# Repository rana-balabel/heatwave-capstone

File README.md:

# HeatWave 🔥

**AI-Powered Heatstroke Prediction Wearable**

University of Waterloo Engineering Capstone Design Project.

HeatWave is a wearable embedded system designed to assess heatstroke
risk using physiological and environmental sensor data.

## Capstone Poster

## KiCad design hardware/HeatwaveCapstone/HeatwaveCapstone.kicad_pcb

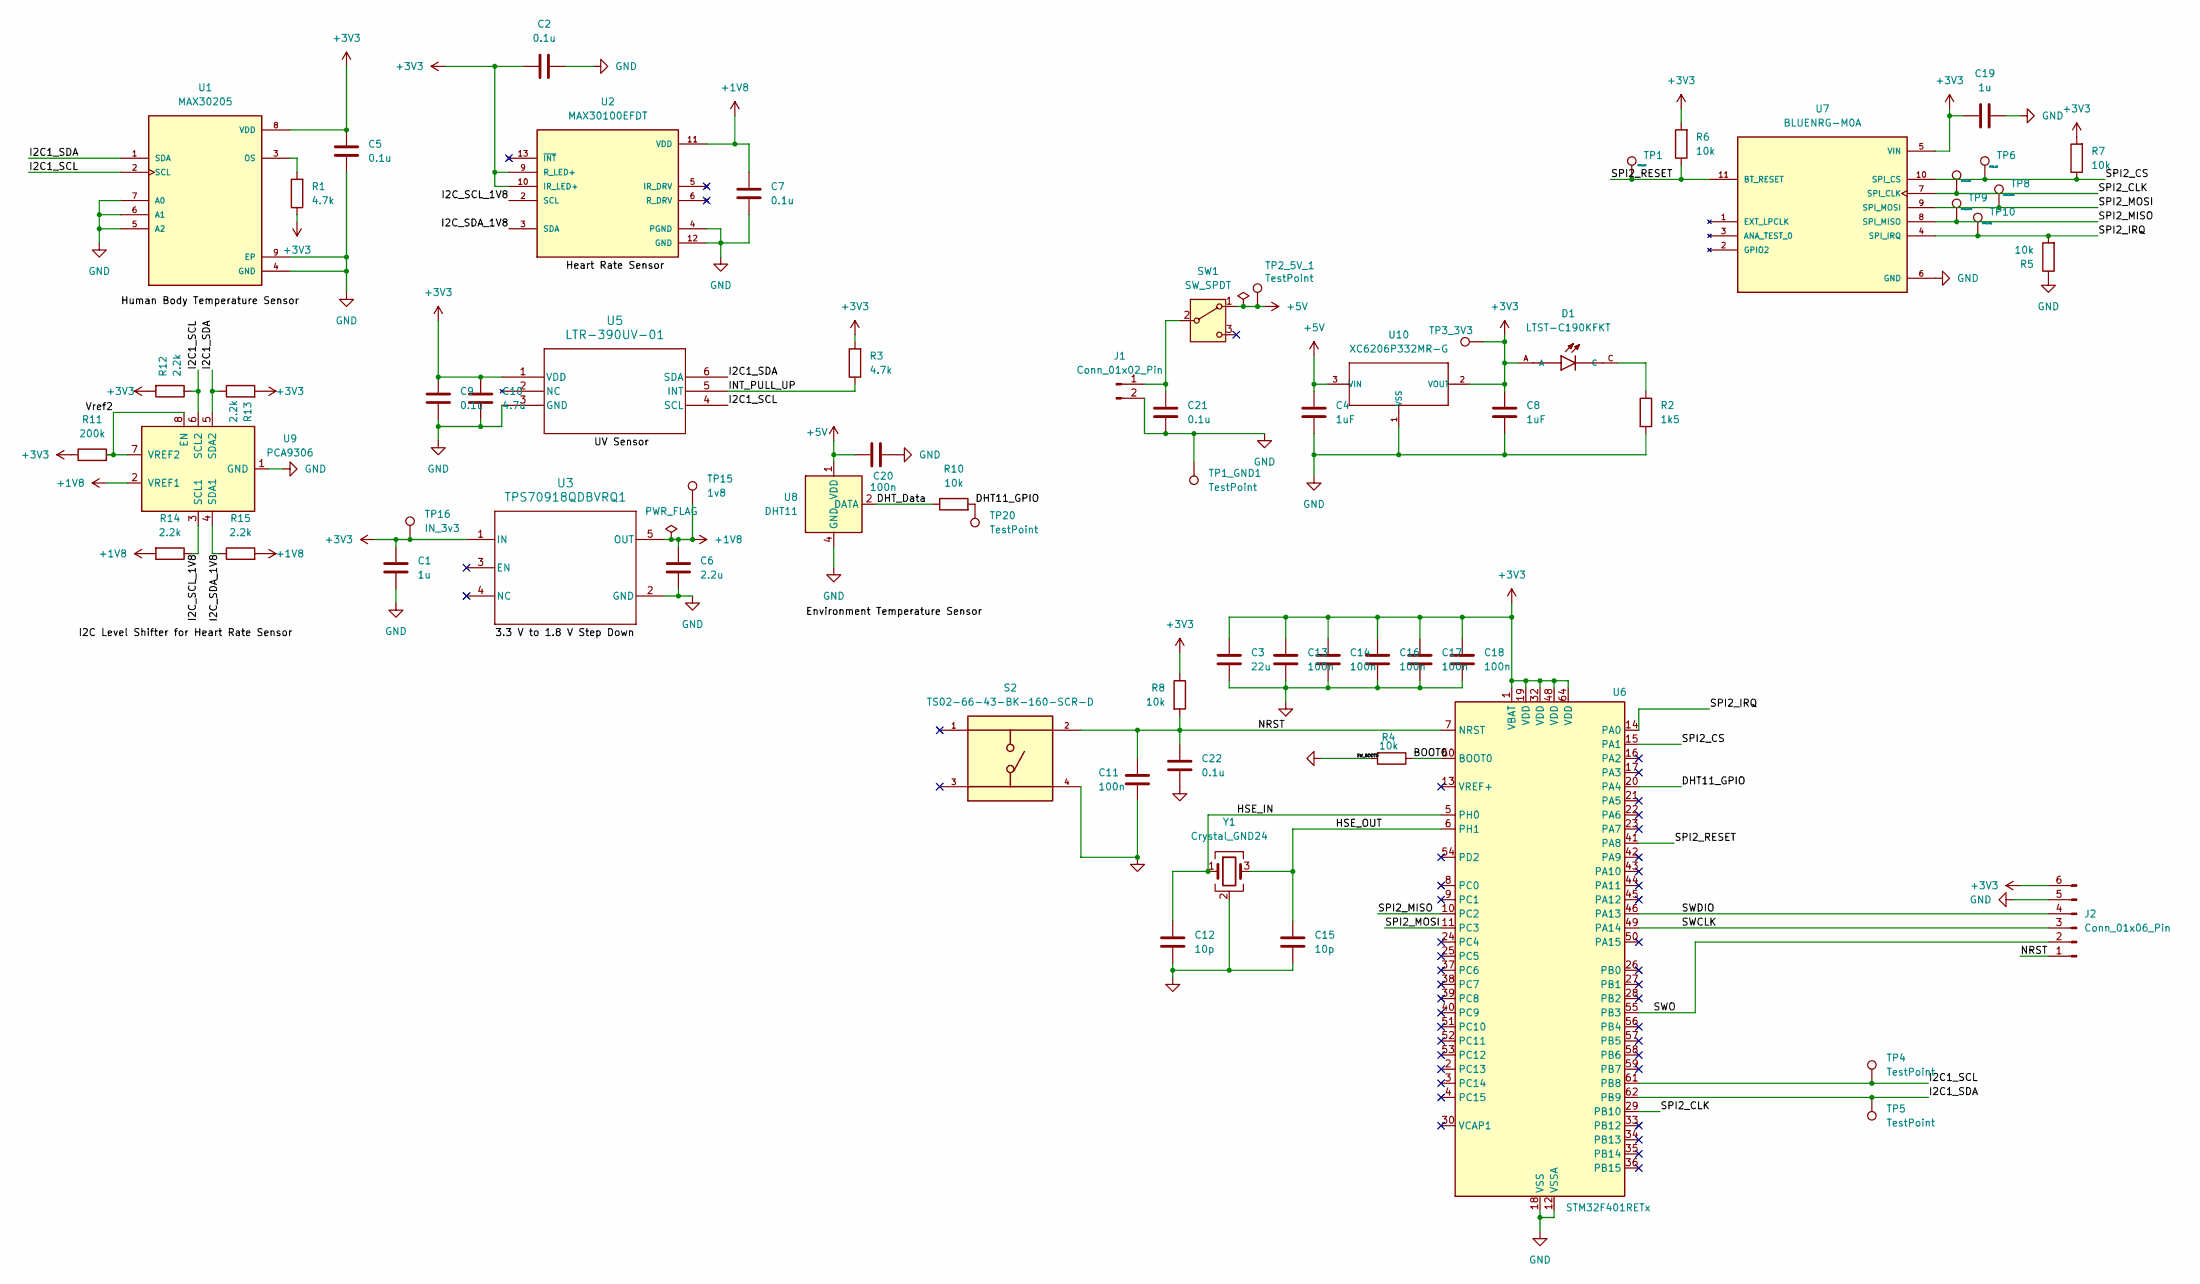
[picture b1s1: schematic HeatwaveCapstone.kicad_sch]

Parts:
C1, C19: 1u; C_0603_1608Metric
C2, C5, C7, C9, C21, C22: 0.1u; C_0603_1608Metric
C3: 22u; C_0603_1608Metric
C4, C8: 1uF; C_0603_1608Metric
C6: 2.2u; C_0603_1608Metric
C10: 4.7u; C_0603_1608Metric
C11, C13, C14, C16, C17, C18, C20: 100n; C_0603_1608Metric
C12, C15: 10p; C_0603_1608Metric
D1: LTST-C190KFKT; LEDM1608X80
J1: Conn_01x02_Pin; PinHeader_1x02_P2.54mm_Vertical
J2: Conn_01x06_Pin; PinHeader_1x06_P2.54mm_Vertical
R1, R3: 4.7k; R_0603_1608Metric
R2: 1k5; R_0603_1608Metric
R4, R5, R6, R7, R8, R10: 10k; R_0603_1608Metric
R11: 200k; R_0603_1608Metric
R12, R13, R14, R15: 2.2k; R_0603_1608Metric
S2: TS02-66-43-BK-160-SCR-D; SW_B3F-1000; PARTREV 1.0
SW1: SW_SPDT; SW_SPDT_CK_JS102011SAQN
TP1, TP6: SPI2_CS; TestPoint_Pad_1.0x1.0mm
TP1_GND1, TP2_5V_1, TP4, TP5, TP20: TestPoint; TestPoint_Pad_1.0x1.0mm
TP3_3V3: TestPoint_Pad_1.0x1.0mm
TP7: SPI2_CLK; TestPoint_Pad_1.0x1.0mm
TP8: SPI2_MOSI; TestPoint_Pad_1.0x1.0mm
TP9: SPI2_MISO; TestPoint_Pad_1.0x1.0mm
TP10: SPI2_IRQ; TestPoint_Pad_1.0x1.0mm
TP15: 1v8; TestPoint_Pad_1.0x1.0mm
TP16: IN_3v3; TestPoint_Pad_1.0x1.0mm
U1: MAX30205; SON65P300X300X80-9N
U2: MAX30100EFDT; LGA14R80P2X7_560X280X130
U3: TPS70918QDBVRQ1; SOT95P280X145-5N
U5: LTR-390UV-01; SMD6_LTR-390UV-01_LTO
U6: STM32F401RETx; LQFP-64_10x10mm_P0.5mm
U7: BLUENRG-M0A; XCVR_BLUENRG-M0A; PARTREV Rev 5
U8: DHT11; Aosong_DHT11_5.5x12.0_P2.54mm
U9: PCA9306; SOP65P400X130-8N
U10: XC6206P332MR-G; SOT-23; MPN XC6206P332MR-G
Y1: Crystal_GND24; XTAL_ABM8-16.000MHZ-10-1-U-T

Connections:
+1V8: C6.1, C7.1, R14.2, R15.2, TP15.1, U2.11 (VDD), U3.5 (OUT), U9.2 (VREF1)
+3V3: C1.1, C2.1, C3.1, C5.1, C8.1, C9.1, C10.1, C13.1, C14.1, C16.1, C17.1, C18.1, C19.1, D1.A, J2.6, R1.1, R3.2, R6.2, R7.2, R8.1, R11.1, R12.2, R13.2, TP3_3V3.1, TP16.1, U1.8 (VDD), U2.9 (R_LED+), U2.10 (IR_LED+), U3.1 (IN), U5.1 (VDD), U6.1 (VBAT), U6.19 (VDD), U6.32 (VDD), U6.48 (VDD), U6.64 (VDD), U7.5 (VIN), U10.2 (VOUT)
+5V: C4.1, C20.1, SW1.1 (A), TP2_5V_1.1, U8.1 (VDD), U10.3 (VIN)
/BOOT0: R4.1, U6.60 (BOOT0)
/DHT11_GPIO: R10.2, TP20.1, U6.20 (PA4)
/DHT_Data: R10.1, U8.2 (DATA)
/HSE_IN: C12.1, U6.5 (PH0), Y1.1
/HSE_OUT: C15.1, U6.6 (PH1), Y1.3
/I2C1_SCL: R12.1, TP4.1, U1.2 (SCL), U5.4 (SCL), U6.61 (PB8), U9.6 (SCL2)
/I2C1_SDA: R13.1, TP5.1, U1.1 (SDA), U5.6 (SDA), U6.62 (PB9), U9.5 (SDA2)
/I2C_SCL_1V8: R14.1, U2.2 (SCL), U9.3 (SCL1); also elsewhere on the board
/I2C_SDA_1V8: R15.1, U2.3 (SDA), U9.4 (SDA1); also elsewhere on the board
/INT_PULL_UP: R3.1, U5.5 (INT)
/NRST: C11.1, C22.2, J2.1, R8.2, S2.2, U6.7 (NRST)
/SPI2_CLK: TP7.1, U6.29 (PB10), U7.7 (SPI_CLK)
/SPI2_CS: R7.1, TP6.1, U6.15 (PA1), U7.10 (SPI_CS)
/SPI2_IRQ: R5.2, TP10.1, U6.14 (PA0), U7.4 (SPI_IRQ)
/SPI2_MISO: TP9.1, U6.10 (PC2), U7.8 (SPI_MISO)
/SPI2_MOSI: TP8.1, U6.11 (PC3), U7.9 (SPI_MOSI)
/SPI2_RESET: R6.1, TP1.1, U6.41 (PA8), U7.11 (BT_RESET)
/SWCLK: J2.3, U6.49 (PA14)
/SWDIO: J2.4, U6.46 (PA13)
/SWO: J2.2, U6.55 (PB3)
/Vref2: R11.2, U9.7 (VREF2), U9.8 (EN)
GND: C1.2, C2.2, C3.2, C4.2, C5.2, C6.2, C7.2, C8.2, C9.2, C10.2, C11.2, C12.2, C13.2, C14.2, C15.2, C16.2, C17.2, C18.2, C19.2, C20.2, C21.2, C22.1, J1.2, J2.5, R2.2, R4.2, R5.1, S2.4, TP1_GND1.1, U1.4 (GND), U1.5 (A2), U1.6 (A1), U1.7 (A0), U1.9 (EP), U2.4 (PGND), U2.12 (GND), U3.2 (GND), U5.3 (GND), U6.12 (VSSA), U6.18 (VSS), U6.31 (VSS), U6.47 (VSS), U6.63 (VSS), U7.6 (GND), U8.4 (GND), U9.1 (GND), U10.1 (VSS), Y1.2 (G), Y1.4 (G)
unnamed: D1.C, R2.1
unnamed: C21.1, J1.1, SW1.2 (B)
unnamed: R1.2, U1.3 (OS)

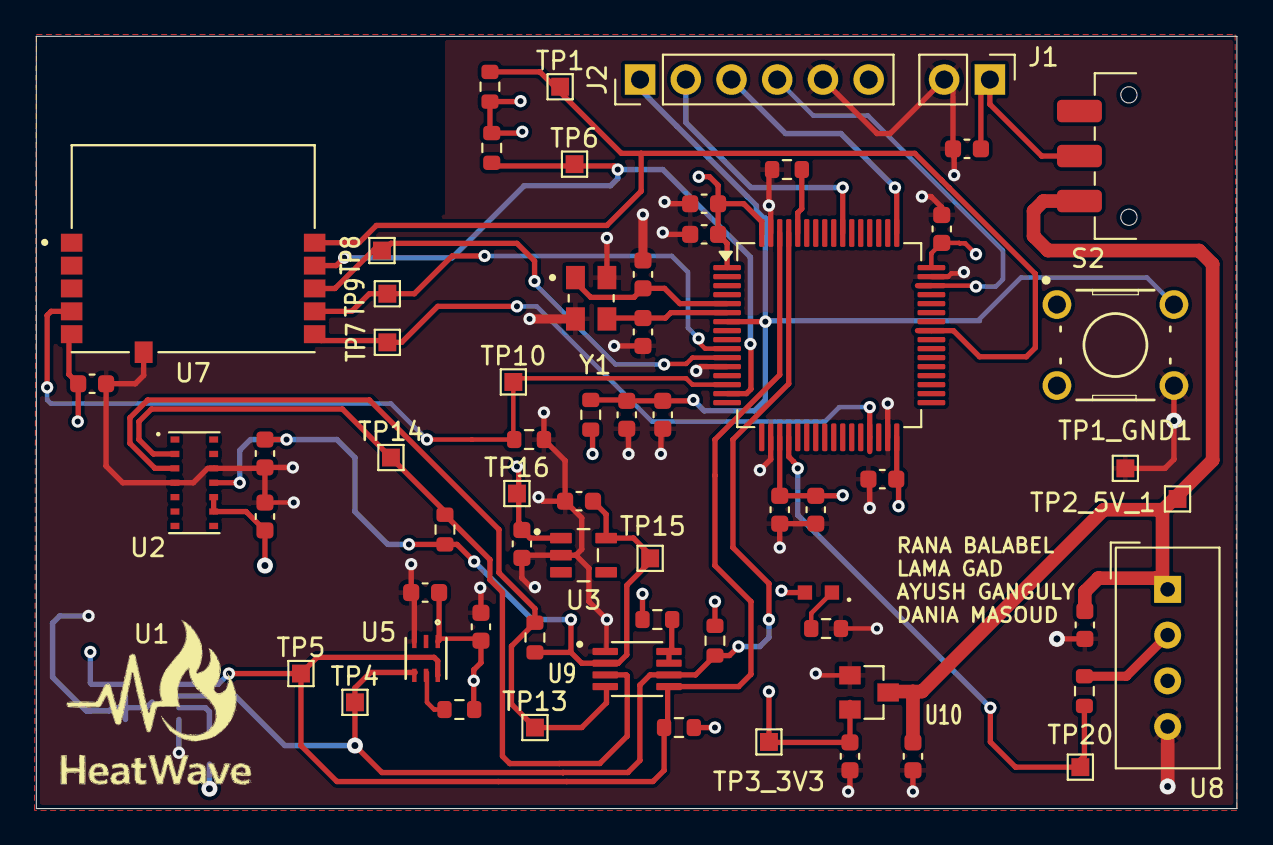
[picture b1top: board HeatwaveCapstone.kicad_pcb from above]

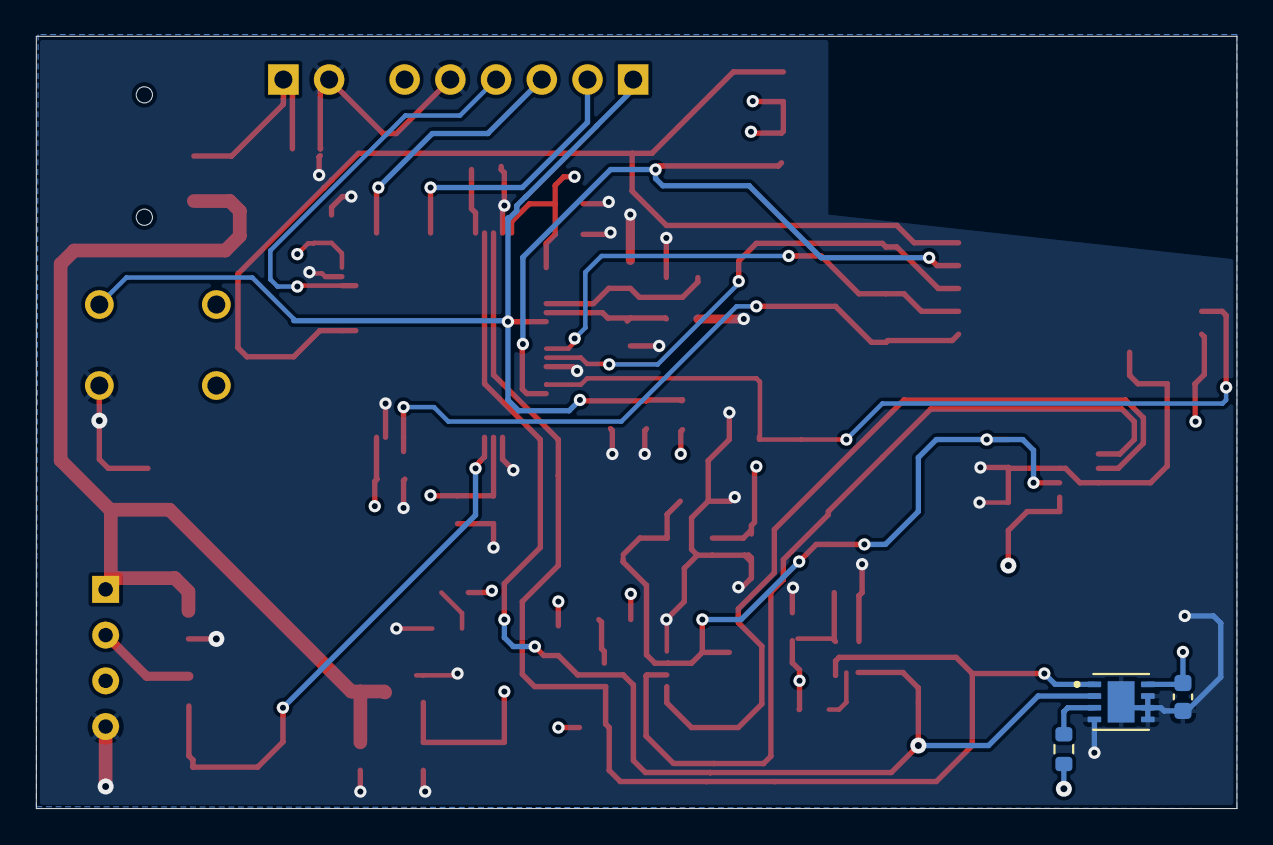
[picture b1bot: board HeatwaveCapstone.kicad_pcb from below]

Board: 4 copper layers, 66.7 x 42.9 mm, 67 parts (3 on the bottom side), 28 nets.

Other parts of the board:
TP13: SDA_1V8; TestPoint_Pad_1.0x1.0mm
TP14: SCL_1V8; TestPoint_Pad_1.0x1.0mm

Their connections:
/I2C_SCL_1V8: TP14.1; also elsewhere on the board
/I2C_SDA_1V8: TP13.1; also elsewhere on the board

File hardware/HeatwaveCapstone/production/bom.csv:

Designator,Footprint,Quantity,Value,LCSC Part #
"C1, C19",0603,2,1u,
C10,0603,1,4.7u,
"C11, C13, C14, C16, C17, C18, C20",0603,7,100n,
"C12, C15",0603,2,10p,
"C2, C21, C22, C5, C7, C9",0603,6,0.1u,
C3,0603,1,22u,
"C4, C8",0603,2,1uF,
C6,0603,1,2.2u,
D1,LEDM1608X80,1,LTST-C190KFKT,
J1,PinHeader_1x02_P2.54mm_Vertical,1,Conn_01x02_Pin,
J2,PinHeader_1x06_P2.54mm_Vertical,1,Conn_01x06_Pin,
"R1, R3",0603,2,4.7k,
"R10, R4, R5, R6, R7, R8",0603,6,10k,
R11,0603,1,200k,
"R12, R13, R14, R15",0603,4,2.2k,
R2,0603,1,1k5,
S2,SW_B3F-1000,1,TS02-66-43-BK-160-SCR-D,
SW1,SW_SPDT_CK_JS102011SAQN,1,SW_SPDT,
"TP1, TP6",TestPoint_Pad_1.0x1.0mm,2,SPI2_CS,
TP10,TestPoint_Pad_1.0x1.0mm,1,SPI2_IRQ,
TP13,TestPoint_Pad_1.0x1.0mm,1,SDA_1V8,
TP14,TestPoint_Pad_1.0x1.0mm,1,SCL_1V8,
TP15,TestPoint_Pad_1.0x1.0mm,1,1v8,
TP16,TestPoint_Pad_1.0x1.0mm,1,IN_3v3,
"TP1_GND1, TP20, TP2_5V_1, TP4, TP5",TestPoint_Pad_1.0x1.0mm,5,TestPoint,
TP3_3V3,TestPoint_Pad_1.0x1.0mm,1,~,
TP7,TestPoint_Pad_1.0x1.0mm,1,SPI2_CLK,
TP8,TestPoint_Pad_1.0x1.0mm,1,SPI2_MOSI,
TP9,TestPoint_Pad_1.0x1.0mm,1,SPI2_MISO,
U1,SON65P300X300X80-9N,1,MAX30205,
U10,SOT-23,1,XC6206P332MR-G,XC6206P332MR-G
U2,LGA14R80P2X7_560X280X130,1,MAX30100EFDT,
U3,SOT95P280X145-5N,1,TPS70918QDBVRQ1,
U5,SMD6_LTR-390UV-01_LTO,1,LTR-390UV-01,
U6,LQFP-64_10x10mm_P0.5mm,1,STM32F401RETx,
U7,XCVR_BLUENRG-M0A,1,BLUENRG-M0A,
U8,Aosong_DHT11_5.5x12.0_P2.54mm,1,DHT11,
U9,SOP65P400X130-8N,1,PCA9306,
Y1,XTAL_ABM8-16.000MHZ-10-1-U-T,1,Crystal_GND24,

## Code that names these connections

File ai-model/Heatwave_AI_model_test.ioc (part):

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Mcu.Name=STM32F401R(D-E)Tx
Mcu.Package=LQFP64
Mcu.UserName=STM32F401RETx
PA0-WKUP.Signal=GPXTI0
PA1.Signal=GPIO_Output
PA13.GPIOParameters=GPIO_Label
PA13.GPIO_Label=TMS
PA13.Mode=Serial_Wire
PA13.Signal=SYS_JTMS-SWDIO
PA14.GPIOParameters=GPIO_Label
PA14.GPIO_Label=TCK
PA14.Mode=Serial_Wire
PA14.Signal=SYS_JTCK-SWCLK
PA2.GPIOParameters=GPIO_Speed,GPIO_PuPd,GPIO_Label,GPIO_Mode
PA2.GPIO_Label=USART_TX
PA2.GPIO_Mode=GPIO_MODE_AF_PP
PA2.GPIO_PuPd=GPIO_NOPULL
PA2.GPIO_Speed=GPIO_SPEED_FREQ_LOW
PA2.Mode=Asynchronous
PA2.Signal=USART2_TX
PA3.GPIOParameters=GPIO_Speed,GPIO_PuPd,GPIO_Label,GPIO_Mode
PA3.GPIO_Label=USART_RX
PA3.GPIO_Mode=GPIO_MODE_AF_PP
PA3.GPIO_PuPd=GPIO_NOPULL
PA3.GPIO_Speed=GPIO_SPEED_FREQ_LOW
PA3.Mode=Asynchronous
PA3.Signal=USART2_RX
PA4.Signal=GPIO_Input
PA5.GPIOParameters=GPIO_Speed,GPIO_PuPd,GPIO_Label,GPIO_Mode
PA5.GPIO_Label=LD2 [Green Led]
PA5.GPIO_Mode=GPIO_MODE_OUTPUT_PP
PA5.GPIO_PuPd=GPIO_NOPULL
PA5.GPIO_Speed=GPIO_SPEED_FREQ_LOW
PA5.Signal=GPIO_Output
PA8.Signal=GPIO_Output
PB10.Mode=Full_Duplex_Master
PB10.Signal=SPI2_SCK
PB5.Signal=GPIO_Input
PB8.Mode=I2C
PB8.Signal=I2C1_SCL
PB9.Mode=I2C
PB9.Signal=I2C1_SDA
PC13-ANTI_TAMP.GPIOParameters=GPIO_PuPd,GPIO_Label,GPIO_ModeDefaultEXTI
PC13-ANTI_TAMP.GPIO_Label=B1 [Blue PushButton]
PC13-ANTI_TAMP.GPIO_ModeDefaultEXTI=GPIO_MODE_IT_FALLING
PC13-ANTI_TAMP.GPIO_PuPd=GPIO_NOPULL
PC13-ANTI_TAMP.Signal=GPXTI13
PC14-OSC32_IN.Mode=LSE-External-Oscillator
PC14-OSC32_IN.Signal=RCC_OSC32_IN
PC15-OSC32_OUT.Mode=LSE-External-Oscillator
PC15-OSC32_OUT.Signal=RCC_OSC32_OUT
PC2.Mode=Full_Duplex_Master
PC2.Signal=SPI2_MISO
PC3.Mode=Full_Duplex_Master
PC3.Signal=SPI2_MOSI
PD2.Signal=GPIO_Input
PH0\ -\ OSC_IN.Mode=HSE-External-Clock-Source
PH0\ -\ OSC_IN.Signal=RCC_OSC_IN
PH1\ -\ OSC_OUT.Mode=HSE-External-Clock-Source
PH1\ -\ OSC_OUT.Signal=RCC_OSC_OUT
RCC.HSE_VALUE=8000000
RCC.SYSCLKFreq_VALUE=84000000
RCC.SYSCLKSource=RCC_SYSCLKSOURCE_PLLCLK
board=NUCLEO-F401RE
boardIOC=true
